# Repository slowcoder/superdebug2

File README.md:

# superdebug2
CMSIS-DAP compatible debug-board w/ UART, power-control, etc

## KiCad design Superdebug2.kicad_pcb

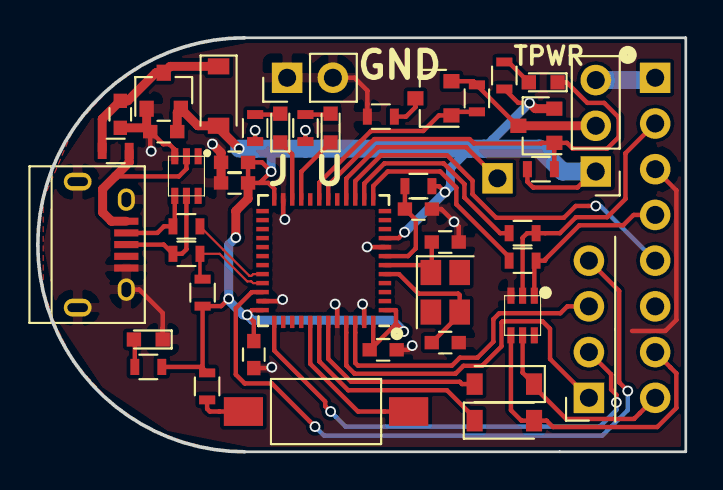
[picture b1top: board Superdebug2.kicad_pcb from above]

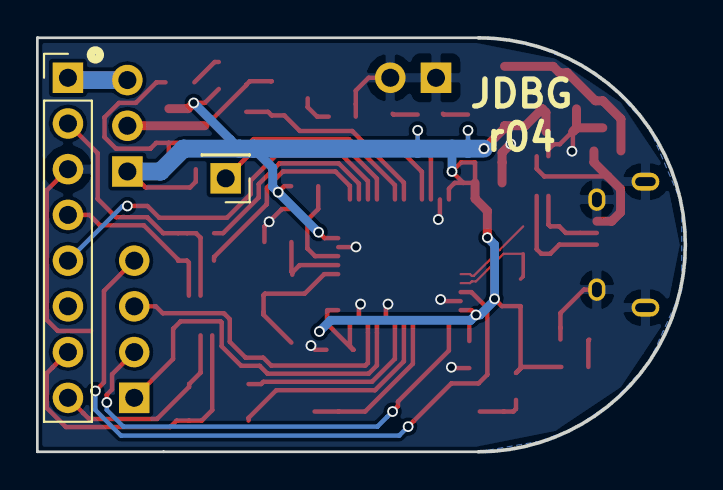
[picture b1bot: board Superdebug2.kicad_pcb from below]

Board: 2 copper layers, 36.0 x 23.0 mm, 45 parts (2 on the bottom side), 38 nets.

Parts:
C1, C8, C9: 10uF; C_0603
C2, C3, C4, C7: 0.1uF; C_0603
C5, C6: 12pF; C_0603
D1: 3V3; LED_0603
D2: SWD; LED_0603
D3: UART; LED_0603
D4: D_Small; D_SOD-123
D5: T_PWR; LED_0603
D6, D7: 0.5V; D_SOD-123
J1: GND; Pin_Header_Straight_1x02_Pitch2.54mm
L1: FB; R_0603
P1: GPIOs; Socket_Strip_Angled_1x04_Pitch2.54mm
P2: USB_OTG; USB_Micro-B
P3: PWR_BYPASS; Pin_Header_Straight_1x03_Pitch2.54mm
P4: JAMESPORT; Pin_Header_Straight_1x08_Pitch2.54mm
P5: PRODTESTPIN; Pin_Header_Straight_1x01_Pitch2.54mm
Q2, Q3: BSS84; SOT-23
R2, R12: 10K; R_0603
R3, R5, R6, R15: 82; R_0603
R4, R13: 1.5K; R_0603
R7, R8: 22; R_0603
R9, R10: 220; R_0603
R11, R14: 100K; R_0603
SW1: PRODTEST; SW_SPST_FSMSM
U1: STM32F103C8T6; QFN-48-1EP_7x7mm_Pitch0.5mm
U2, U5: TPD4E1B06; TI_DCK_(R-PDSO-G6)
U4: MCP1700T-3302; SOT-23
Y1: 16MHz; Crystal_SMD_SeikoEpson_TSX3225-4pin_3.2x2.5mm

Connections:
+5V: C8.1, D4.1, L1.1, U4.3
/LED_SWD: D2.1, U1.22
/LED_UART: D3.1, U1.21
/OWN_SWCLK: P1.2, U1.37
/OWN_SWDIO: P1.4, U1.34
/T_DRAINCAPS: Q3.1, R11.2, U1.19
/T_GPIO0: P1.1, U1.45
/T_GPIO2: P1.3, U1.46
/T_NRST: P4.5, U1.15
/T_PRODTEST: P5.1, U1.16
/T_PWR: D5.1, Q2.1, R14.2, U1.18
/T_RX: D7.2, U1.43
/T_SWCLK: R9.1, U1.14
/T_SWDIO: R10.2, U1.13
/T_TX: D6.1, U1.42
/USB_D+: R4.2, R7.1, U1.33
/USB_D-: R8.2, U1.32
/VDUT: P3.3, P4.1
/VSW: P3.2, Q2.3, Q3.2, R11.1
GND: C1.2, C2.2, C3.2, C4.2, C5.2, C6.2, C7.2, C8.2, C9.2, D1.1, J1.1, J1.2, P2.5, P2.6, P4.3, R12.2, U1.8, U1.23, U1.35, U1.44, U1.47, U2.3, U4.1, U5.3
unnamed: C5.1, U1.6, Y1.1
unnamed: C6.1, U1.5, Y1.3
unnamed: C7.1, R2.1, U1.7
unnamed: D1.2, R3.2
unnamed: D2.2, R5.2
unnamed: D3.2, R6.2
unnamed: D5.2, R15.2
unnamed: D6.2, P4.7, U5.4
unnamed: D7.1, P4.8, U5.5
unnamed: L1.2, P2.1, U2.2
unnamed: P2.2, R8.1, U2.4
unnamed: P2.3, R7.2, U2.5
unnamed: P4.2, R9.2, U5.2
unnamed: P4.4, R10.1, U5.1
unnamed: Q3.3, R12.1
unnamed: R13.2, SW1.1
unnamed: SW1.2, U1.41
VDD: C1.1, C2.1, C3.1, C4.1, C9.1, D4.2, P3.1, Q2.2, R2.2, R3.1, R4.1, R5.1, R6.1, R13.1, R14.1, R15.1, U1.1, U1.9, U1.24, U1.36, U1.48, U4.2
